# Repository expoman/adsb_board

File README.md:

# adsb_board
small PCB with filter and lna for adsb-signals

# used components

as filter two ta1090ec are used

# results

the assembled board was tested with an vector-network analyzer

the bandpass is narrow as expected and the lna-boosts the signal nicely

screenshots are saved under results

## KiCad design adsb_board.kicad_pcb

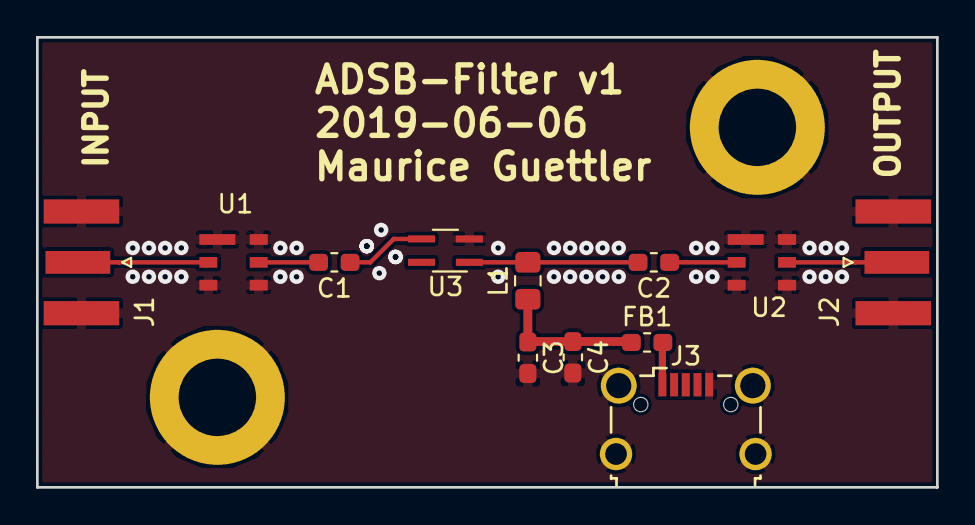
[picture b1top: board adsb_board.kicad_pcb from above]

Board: 2 copper layers, 50.0 x 25.0 mm, 14 parts (0 on the bottom side), 9 nets.

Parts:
C1, C2: 150pF; C_0603_1608Metric_Pad1.05x0.95mm_HandSolder
C3: 1000pF; C_0603_1608Metric_Pad1.05x0.95mm_HandSolder
C4: 4.7uF; C_0603_1608Metric_Pad1.05x0.95mm_HandSolder
FB1: Ferrite_Bead; R_0603_1608Metric_Pad1.05x0.95mm_HandSolder
H1, H2: MountingHole_Pad; MountingHole_4.3mm_M4_DIN965_Pad
J1, J2: Conn_Coaxial; SMA_Samtec_SMA-J-P-H-ST-EM1_EdgeMount
J3: USB_B_Micro; USB_Micro-B_Wuerth_629105150521_CircularHoles
L1: 22nH; L_0805_2012Metric_Pad1.15x1.40mm_HandSolder
U1, U2: TA1090EC; ta1090ec
U3: PSA4-5043+; SOT-343_SC-70-4_Handsoldering

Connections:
/GND: C3.2, C4.2, H1.1, H2.1, J1.2, J2.2, J3.5, J3.6, U1.1, U1.3, U1.4, U1.6, U2.1, U2.3, U2.4, U2.6, U3.2
/INPUT: J1.1, U1.2
/OUTPUT: J2.1, U2.5
/VCC: C3.1, C4.1, FB1.1, L1.1
unnamed: C1.1, U3.3
unnamed: C1.2, U1.5
unnamed: C2.1, U2.2
unnamed: C2.2, L1.2, U3.1
unnamed: FB1.2, J3.1

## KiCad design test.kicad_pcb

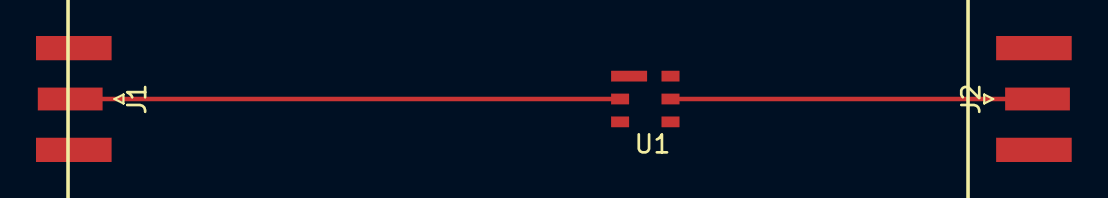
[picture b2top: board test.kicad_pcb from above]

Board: 2 copper layers, 3 parts (0 on the bottom side), 3 nets.

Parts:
J1, J2: Conn_Coaxial; SMA_Samtec_SMA-J-P-H-ST-EM1_EdgeMount
U1: TA1090EC; ta1090ec

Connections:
GND: J1.2, J2.2, U1.1
unnamed: J1.1, U1.2
unnamed: J2.1, U1.5

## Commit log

2019-03-29 - add four mounting holes m4
    - improve layout (with gnd-planes)
2019-03-29 first draft with kicad files
2019-03-29 prettify schematic
2019-03-29 more improvements
2019-03-29 rename files
2019-03-29 change board size to 50x50mm
2019-03-29 reduced size further to 50x25mm
2019-05-23 remove two mounting holes
2019-05-31 routed first draft of adsb-board
2019-06-03 add psa4-5043+ lna between the two filters
2019-06-03 changes to schematic:
    - add psa4-5034+
    - add cap, inductor values
    - add usb connector from wuerth
2019-06-03 place new components
2019-06-05 update scheamtic
    add vias along the signal trace in the layout
2019-06-05 change shape clearance on top to 200um
2019-06-05 add ferrite bead in supply line
2019-06-06 change usb connector to type with circular holes
2019-06-06 improve silkscreen
2019-06-07 final changes - move sma connectors to board edge
    - changes properties of bottom gnd shape
    - move refdes of sma connectors
2019-11-11 add vna results
2019-11-11 fix image path in README.md
2019-11-11 add filter description to the README.md
